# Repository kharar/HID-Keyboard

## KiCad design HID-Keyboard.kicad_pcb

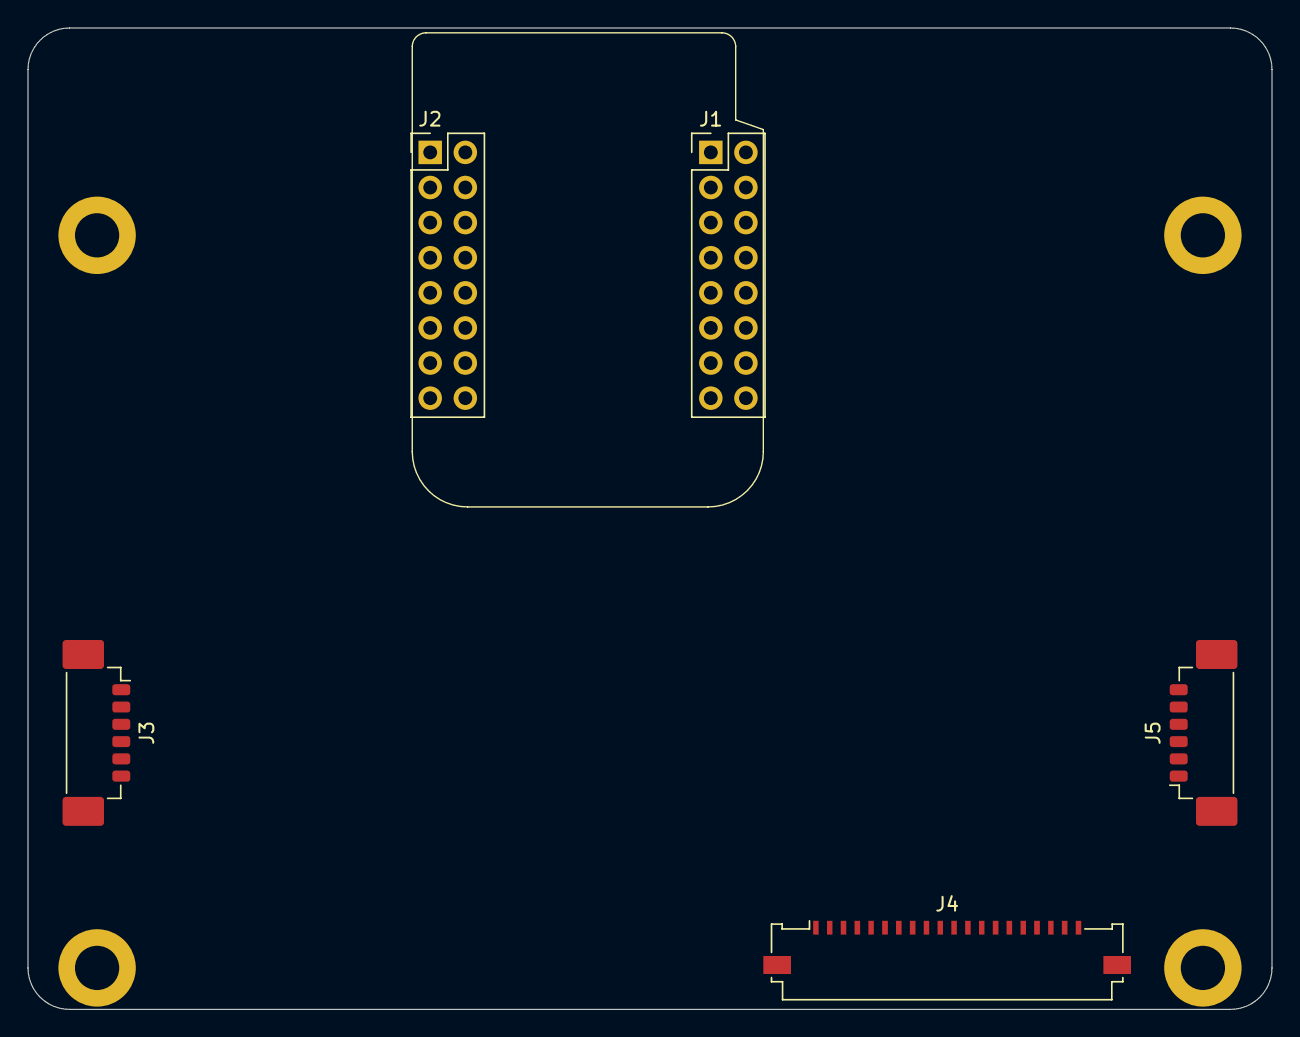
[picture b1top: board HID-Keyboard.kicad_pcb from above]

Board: 2 copper layers, 90.0 x 71.0 mm, 10 parts (0 on the bottom side), 2 nets, no tracks yet.

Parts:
H1, H2, H3, H4: MountingHole_Pad; MountingHole_3.2mm_M3_DIN965_Pad
J1, J2: Conn_02x08_Odd_Even; PinHeader_2x08_P2.54mm_Vertical
J3, J5: Molex 53398-0671; Molex_PicoBlade_53398-0671_1x06-1MP_P1.25mm_Vertical
J4: Molex 200528-0200; Molex_200528-0200_1x20-1MP_P1.00mm_Horizontal
M1: Wemos S2 Mini ESP32; Wemos S2 Mini

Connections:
GND: H1.1, H2.1, H3.1, H4.1, J2.3, J2.4, J3.MP (MountPin), J4.MP (MountPin), J5.MP (MountPin)
unnamed: J4.1, J4.2

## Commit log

2025-09-02 Arduino sketch and KiCAD project initiated
2025-09-03 Add & place core footprints
2025-09-23 swap designators
2025-09-23 port sketch to Lolin S2 Mini ESP32
2025-09-23 ignore zip files
2025-09-23 Remove zip files
2025-09-23 Add Wemos S2 Mini footprint & 3D model
2025-10-05 Add 5V to 3.3V signal circuit
2025-10-15 Schematic: add more documentation
